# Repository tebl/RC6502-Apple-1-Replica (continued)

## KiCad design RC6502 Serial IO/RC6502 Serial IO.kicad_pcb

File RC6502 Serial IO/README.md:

# RC6502 Serial IO

The original Apple 1 computer had circuitry for displaying data on a monitor as well as reading input via a physical keyboard, but to keep things simple we are instead using an Arduino Nano to this! Might not be as cool without an antique keyboard or a big and scary CRT monitor connected to it, but then again those things aren't for beginners and should you feel like adding them later there no reason as to why you can't!

Via the Arduino Nano we can communicate with the computer, the one you'¨ve just built, by using your favourite terminal emulator program such as PuTTy, SecureCRT or similar over the serial interface provided by the Nano. The Nano will of course need some software running on it, you'll find that in the form of an Arduino sketch called "[PIA Communicator](https://github.com/tebl/RC6502/tree/master/RC6502%20Serial%20IO/pia_communicator)". This is a rather basic version of that is intended to get you started with something that is easy to understand, thanks however to the wonders of the Internet and collaborative forces of Github you can find a much improved version of it on [https://github.com/jblang/pia_communicator](https://github.com/jblang/pia_communicator).

The RC6502 computer, more specifically this module or the one integrated into the [SBC](https://github.com/tebl/RC6502-Apple-1-Replica/tree/master/RC6502%20Apple%201%20SBC) version of it has an IC called a PIA (Peripheral Interface Adapter) on it. The PIA has two ports and when Wozniak his original Apple 1, he dedicated one port to video output and the other to keyboard input - both of those functions we've replaced with our Nano, but to keep things original we've kept the actual PIA to keep things authentic. A 40-pin headers in addition to a couple of pull-up resistors have been added to the board so that one or both of these can be later replaced with actual hardware.

You have several options for which particular type of PIA to use, there is the MC6820, MC6821 as well as the newer W65c21 that are available. The ones I've had most luck with, and to me feels the most authentic has to be the MC6821 by Motorola - a slightly newer design than the original MC6820, but it's more abundantly available for purchase while still featured in most older computer design books so that is the one I prefer to use.

The serial module works by replacing all of this so that characters are transferred using the serial communications functionality on an Arduino Nano board. To make things easier when communicating with parallell devices using a Nano, I've added an IO-expander in the form of the SPI-based MCP23S17 (see [Githup Repository](https://github.com/MajenkoLibraries/MCP23S17) for the library needed).

# Schematic
The supplied KiCad files should be sufficient as both a schematic and as a starting
point for ordering PCBs, the schematic is also available in
[PDF-format](https://github.com/tebl/RC6502/raw/master/RC6502%20Serial%20IO/export/RC6502%20Serial%20IO.pdf). You can refer to the BOM below for a list of suggested components to use, part numbers in parenthesis are optional and is not required.

# BOM
These are the components needed to put together your very own Serial IO-module for the RC6502 computer, should be able to get most from your favourite parts supplier though the older PIAs I had to purchase via AliExpress/ebay since they aren't stocked anymore by the other monopolies (atleast where I live). For the pin headers, both male and female - if you can't find the exact pin count, just buy the longer versions and snip/cut off the parts you don't need (get extra in case of accidents, and don't cut yourself either!). As previously mentioned, part counts in parenthesis are to be considered optional so feel free to leave them out if you don't have any specific plans for them.

| Reference | Item                                  | Count  |
| --------- | ------------------------------------- | ------ |
| PCB       | Fabricate yourself using KiCad files  |     1  |
| U1        | 74LS04                                |     1  |
| U2        | MC6821 PIA                            |     1  |
| U3        | 74LS138                               |     1  |
| C1-C3     | 100nF ceramic capacitor               |     3  |
| C4        | 10nF ceramic capacitor                |     1  |
| R1-R5     | Resistor, 10K (R1,R4 optional)        |  3 (2) |
| J1        | 1x39 right angle pin header, male     |     1  |
| J2        | Arduino pin headers, 1x15 pin header  |     2  |
| J3        | 1x5 right angle pin header, male      |    (1) |
| J4        | 2x20 pin header, male                 |    (1) |
| JP1       | 1x2 right angle pin header, male      |     1  |
| SW1       | PCB momentary push button             |     1  |
| Nano      | Arduino Nano with data cable          |     1  |

If you would like to have a copy of one or more modules, what you'll need to do is zip up the contents of the export directory for each module and give that to your favourite PCB fabrication plant. Personally I prefer to use [PCBWay](https://www.pcbway.com/setinvite.aspx?inviteid=88707), each module has been designed to fit inside the 5$ dimensions. Use the link provided when signing up to support this project!

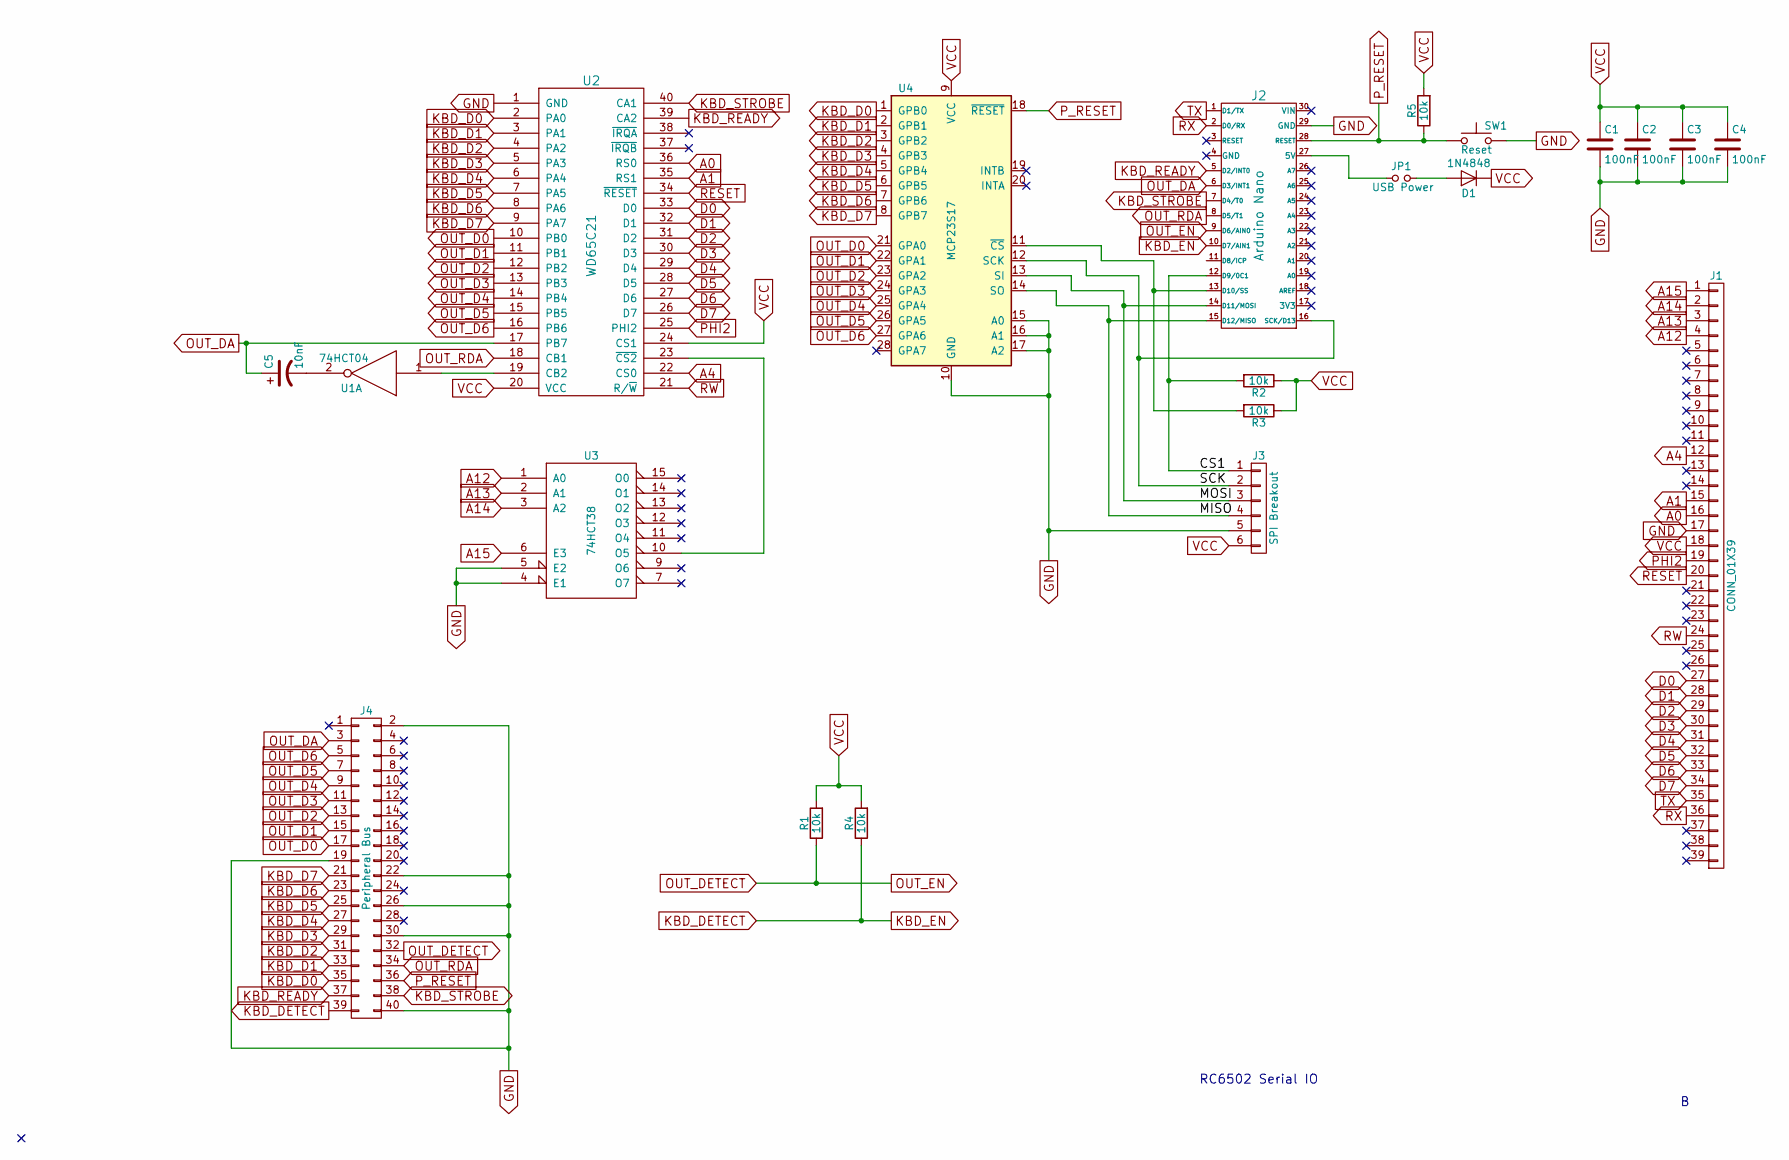
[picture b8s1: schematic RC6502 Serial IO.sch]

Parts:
C1, C2, C3, C4: 100nF; C_Disc_D4.7mm_W2.5mm_P5.00mm
C5: 10nF; C_Disc_D4.7mm_W2.5mm_P5.00mm
D1: 1N4848; D_DO-35_SOD27_P7.62mm_Horizontal
J1: CONN_01X39; Pin_Header_Angled_1x39_Pitch2.54mm
J2: Arduino Nano; Arduino_Nano
J3: SPI Breakout; Pin_Header_Angled_1x06_Pitch2.54mm
J4: Peripheral Bus; IDC_Header_Straight_40pins
JP1: USB Power; Pin_Header_Angled_1x02_Pitch2.54mm
R1, R2, R3, R4, R5: 10k; R_Axial_DIN0207_L6.3mm_D2.5mm_P10.16mm_Horizontal
SW1: Reset; SW_PUSH_6mm
U1: 74HCT04; DIP-14_W7.62mm_Socket
U2: WD65C21; DIP-40_W15.24mm_Socket
U3: 74HCT38; DIP-16_W7.62mm_Socket
U4: MCP23S17; DIP-28_W7.62mm_Socket

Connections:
/CS1: J2.12 (D9/0C1), J3.1, R2.2
/MISO: J2.15 (D12/MISO), J3.4, U4.14 (SO)
/MOSI: J2.14 (D11/MOSI), J3.3, U4.13 (SI)
/SCK: J2.16 (SCK/D13), J3.2, U4.12 (SCK)
A0: J1.16, U2.36 (RS0)
A1: J1.15, U2.35 (RS1)
A4: J1.12, U2.22 (CS0)
A12: J1.4, U3.1 (A0)
A13: J1.3, U3.2 (A1)
A14: J1.2, U3.3 (A2)
A15: J1.1, U3.6 (E3)
D0: J1.27, U2.33 (D0)
D1: J1.28, U2.32 (D1)
D2: J1.29, U2.31 (D2)
D3: J1.30, U2.30 (D3)
D4: J1.31, U2.29 (D4)
D5: J1.32, U2.28 (D5)
D6: J1.33, U2.27 (D6)
D7: J1.34, U2.26 (D7)
GND: C1.2, C2.2, C3.2, C4.2, J1.17, J2.29 (GND), J3.5, J4.2, J4.19, J4.22, J4.26, J4.30, J4.40, SW1.2, U1.7 (GND), U2.1 (GND), U3.4 (E1), U3.5 (E2), U3.8 (GND), U4.10 (GND), U4.15 (A0), U4.16 (A1), U4.17 (A2)
KBD_D0: J4.35, U2.2 (PA0), U4.1 (GPB0)
KBD_D1: J4.33, U2.3 (PA1), U4.2 (GPB1)
KBD_D2: J4.31, U2.4 (PA2), U4.3 (GPB2)
KBD_D3: J4.29, U2.5 (PA3), U4.4 (GPB3)
KBD_D4: J4.27, U2.6 (PA4), U4.5 (GPB4)
KBD_D5: J4.25, U2.7 (PA5), U4.6 (GPB5)
KBD_D6: J4.23, U2.8 (PA6), U4.7 (GPB6)
KBD_D7: J4.21, U2.9 (PA7), U4.8 (GPB7)
KBD_DETECT: J2.10 (D7/AIN1), J4.39, R4.1
KBD_READY: J2.5 (D2/INT0), J4.37, U2.39 (CA2)
KBD_STROBE: J2.7 (D4/T0), J4.38, U2.40 (CA1)
unnamed: C5.2, U1.2
unnamed: D1.2 (A), JP1.2
unnamed: J2.13 (D10/SS), R3.2, U4.11 (~CS)
unnamed: J2.27 (5V), JP1.1
unnamed: U1.1, U2.19 (CB2)
unnamed: U2.23 (~CS2), U3.10 (O5)
OUT_D0: J4.17, U2.10 (PB0), U4.21 (GPA0)
OUT_D1: J4.15, U2.11 (PB1), U4.22 (GPA1)
OUT_D2: J4.13, U2.12 (PB2), U4.23 (GPA2)
OUT_D3: J4.11, U2.13 (PB3), U4.24 (GPA3)
OUT_D4: J4.9, U2.14 (PB4), U4.25 (GPA4)
OUT_D5: J4.7, U2.15 (PB5), U4.26 (GPA5)
OUT_D6: J4.5, U2.16 (PB6), U4.27 (GPA6)
OUT_DA: C5.1, J2.6 (D3/INT1), J4.3, U2.17 (PB7)
OUT_DETECT: J2.9 (D6/AIN0), J4.32, R1.1
OUT_RDA: J2.8 (D5/T1), J4.34, U2.18 (CB1)
PHI2: J1.19, U2.25 (PHI2)
P_RESET: J2.28 (RESET), J4.36, R5.1, SW1.1, U4.18 (~RESET)
RESET: J1.20, U2.34 (~RESET)
RW: J1.24, U2.21 (R/~W)
RX: J1.36, J2.2 (D0/RX)
TX: J1.35, J2.1 (D1/TX)
VCC: C1.1, C2.1, C3.1, C4.1, D1.1 (K), J1.18, J3.6, R1.2, R2.1, R3.1, R4.2, R5.2, U1.14 (VCC), U2.20 (VCC), U2.24 (CS1), U3.16 (VCC), U4.9 (VCC)

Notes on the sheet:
RC6502 Serial IO

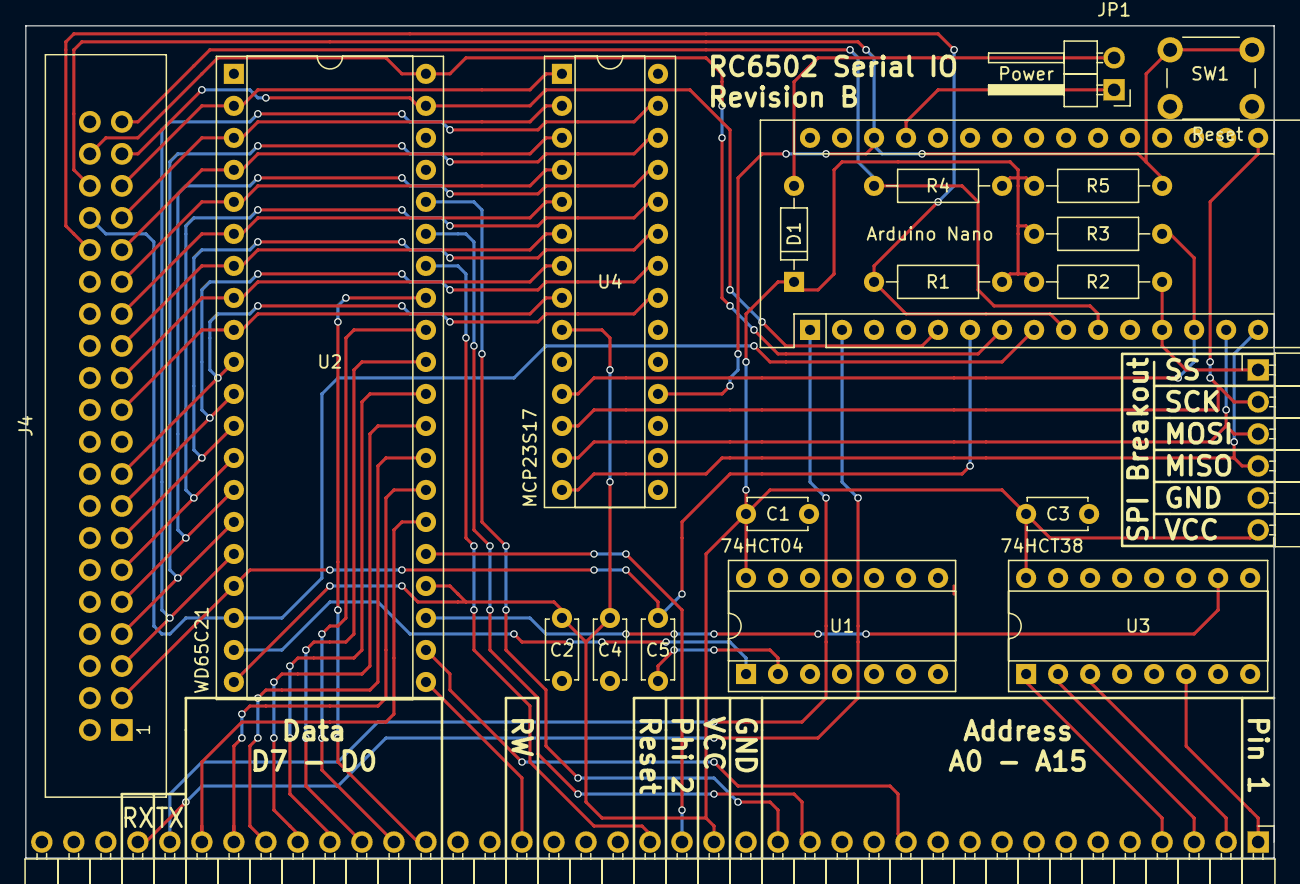
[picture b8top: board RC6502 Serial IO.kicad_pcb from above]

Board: 2 copper layers, 99.1 x 66.0 mm, 21 parts (0 on the bottom side), 54 nets.
